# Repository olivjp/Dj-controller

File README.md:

# Pioneer DDJ-FLX4 Modular Core v2.3 — Open-Source 2-Deck USB-MIDI DJ Controller

Hardware (**KiCad 9.0** `98 × 98 mm` 2-Layer Core PCB — **0 ERC / 0 DRC / 0 unconnected**, ~US\$ 2 na JLCPCB), chassi 3D imprimível em PLA (**FreeCAD 1.0** `.step`/`.stl` em 3 módulos `≤ 115 × 206 mm` compatíveis com cama `220 × 220 mm`, **0 colisões P0** após 3 rodadas independentes de auditoria), e firmware USB-MIDI nativo (**ATmega32U4** com ISRs `PIND` atômicas, varredura Gray, Pitch 14-bit e script JS para **Mixxx 2.4+**).

---

## 1. Visual Previews

### KiCad 9.0 3D Raytraced Core PCB (`98 × 98 mm`, 2-Layer FR4, Solid `B.Cu` GND Plane)

### FreeCAD 1.0 3D-Printable Enclosure Assembly (`340 × 206 × 45.5 mm`)

---

## 2. Arquitetura Modular Core v2.3 (Consolidada após 3 Rodadas de Auditoria)

1. **Placa-Mãe Central `98 × 98 mm`, 2 Camadas (`100% THT 2.54 mm`):**
   - **Arduino Pro Micro USB-C (`J1`/`J2`):** `RAW` (`J2.1`) e `RST` (`J2.3`) desconectados (`NC`).
   - **2× Módulos Breakout Azuis `CD74HC4067` (`J3/J4` = `U1` Analógico com `C15` no topo; `J5/J6` = `U2` Pads girado `180°` com `C0` no topo):** casados 1:1 com o módulo azul físico (`1×16` `C15..C0` + `1×8` `SIG, S3, S2, S1, S0, EN, VCC, GND` alinhado a `C11..C4`, passo `15.24 mm`). *Fazer teste de continuidade A1 antes de subir o Gerber.*
   - **Front-End Analógico Baixo-Crosstalk:** `16×` capacitores `100 nF` (`C10..C25`) **ANTES** do multiplexador `U1` + `R1 = 100 Ω` com **`C3 = DNP`** (não montar `C3`, mantendo o resíduo de carga em `0.22–0.37 LSB` em vez de `3.6–6.2 LSB`).
   - **Debounce de Encoders Padrão Alps (`ENC1`/`ENC2`):** `10 kΩ` pull-up (`R3..R6`) + `10 kΩ` série anti-pitting (`R12..R15`) + `10 nF` (`C4..C7`), compatível com os limiares LVTTL reais do ATmega32U4 ($V_{IL} \le 0.90\text{ V}$, $V_{IH} \ge 1.90\text{ V}$).
   - **Plano de Terra Sólido (`B.Cu`):** `0` violações DRC, `0` itens desconectados (`hardware/gerbers/ddj_flx4_core_v2_jlcpcb.zip`).
2. **Chassi 3D Modular v2.3 (`340 × 206 × 45.5 mm`, `BOTTOM_H = 42 mm`) — 0 Colisões P0:**
   - **PCB recuada `0.5 mm` da parede traseira (`PCB_Y_REAR = 201.5 mm`):** furos traseiros `H1/H2` (`126.08, 196.42` / `213.71, 196.42`) usam **`M3×12` cabeça cilíndrica por baixo** + **espaçador de latão F-F `M3×30` (`5.5 AF`)** + boss `Ø 7 × 1.4 mm` sob a faceplate (`M3×10` escareado por cima). Tirar a tampa não solta a PCB e mantém `+0.71..+1.21 mm` de folga até `RV1/RV6`.
   - **Lábio (`WALL_T + 0.5 mm`) e nervuras de emenda com alívio `Ø 11 mm`** nos 10 pilares + `H1/H2`.
   - **Recorte USB-C alinhado em `Z = -25.2 .. -9.2 mm`** (acomoda overmold até `8.5 mm`).
   - **6 Carriers rígidos com orelhas (`ddj_flx4_switch_carriers.stl`):** `deckA_frente`, `deckB_frente`, `mixer_top`, `mixer_cue`, `loopsync_A`, `loopsync_B`, base `±8.2 mm` (parede sólida por fora dos rasgos de pinos `±7.15 mm`), todos os 30 switches dentro da envoltória convexa de apoio (`margem ≥ +1.0 mm`, alcance `≤ 14.9 mm`), empacotamento automático sem sobreposição, `CARRIER_STANDOFF_H = 4.5 mm` (ajustar para `5.6 mm` se o atuador `G82` medir `≥ Ø 7.2 mm`).
   - **Jog Wheels (`Ø 84 mm`) + Faceplate cheia (`3.5 mm`, sem rebaixo `Ø 86`):** trava de porca `M3` em `r = 6.8..9.2 mm` (livre do rebaixo sob o cubo `Ø 12.5 × 4.0 mm`), canal de acesso `Ø 3.4 mm` para **grub `M3×8`**.
   - **Emendas:** blocos até `Z = -3.0 mm` apoiando as nervuras da faceplate + **4× `M3×12` horizontais por emenda** (`Y = 28` em `Z = -8, -34`; `Y = 178` em `Z = -8, -20` — livres da PCB, de `J9/J10` e de `loopsync_B`).
3. **Firmware USB-MIDI v2.3 + Mixxx 2.4+ (`firmware/`):**
   - Varredura do mux em **código Gray cíclico** (`{0,1,3,2,6,7,5,4,12,13,15,14,10,11,9,8}` — sempre 1 bit por troca entre `PD4/PC6/PD7/PE6`).
   - **`#define HAS_RV16 0`:** pula *apenas* o bloco analógico de `U1` no canal `15` (mantém `SW16` / Pad 8 Deck B e a sequência Gray intactos; nunca usar jumper em `POT_CH15`).
   - **Matriz 4×4 em Open-Drain:** linhas inativas em `INPUT` (Hi-Z), eliminando risco de curto `> 40 mA` caso um diodo `1N4148` fique invertido.
   - **Histerese aplicada sobre o `filtered` cru antes da LUT**, linearização nos **5 faders `D103`** (`CH10..CH14`), zona morta central no Pitch 14-bit (`0xE0`/`0xE1`), `beatloop_toggle` e `SMART_CFX`/`BEAT_FX` nos 2 decks no Mixxx.

---

## 3. Checklist de Bancada (Antes de Fabricar / Imprimir)

| # | Medição física | Objetivo |
|---|---|---|
| **A1** | Módulo azul `CD74HC4067`: encaixe a seco (componentes p/ cima, `1×16` à esquerda, USB-C longe de você $\rightarrow$ canto superior = `C15` alinhado a `SIG`) + continuidade `GND↔pino 12`, `C0↔9`, `C15↔16` e passo `15.24 mm` | **P0** — Libera `ddj_flx4_core_v2_jlcpcb.zip` na JLCPCB |
| **A2** | Diâmetro do atuador do switch `G82` | `CARRIER_STANDOFF_H = 4.5 mm` (`< Ø 7.2`) ou `5.6 mm` (`≥ Ø 7.2`) |
| **A3** | Altura do `WH148` + fio soldado abaixo da faceplate + diâmetro real do corpo (`r ≤ 8.5 mm`) | Folga em Z = `0.8 mm` (se `> 16 mm`, dobrar terminais ou usar `BOTTOM_H = 44`) |
| **A4** | `EC11`: comprimento da bucha M7, comprimento do eixo (`15` vs `20 mm`) e trecho D-flat | Confirmar `JOG_Z` e cota `Z = 4.5 mm` do grub `M3×8` |
| **A5** | Medir fader `D103` no multímetro a `0 / 25 / 50 / 75 / 100%` | Ajustar `LOG_INV_LUT` (ou desligar `LINEARIZE_D103_LOG_FADERS` se linear) |

---

## 4. Bill of Materials (BOM v2.3)

### Na Placa-Mãe Central (`98 × 98 mm` — `hardware/gerbers/ddj_flx4_core_v2_jlcpcb.zip`)
| Designator | Qty | Componente | Observação |
| :--- | :---: | :--- | :--- |
| `J1`, `J2` | 1 | **Arduino Pro Micro USB-C (`ATmega32U4 5V 16MHz`)** + 2× barras fêmea `1×12` | Soquetado rente à borda traseira |
| `J3/J4`, `J5/J6` | 2 | **Módulo Breakout `CD74HC4067` (16-ch, 2.54mm THT)** + barras fêmea `1×16` & `1×8` | `U2` montado girado `180°` |
| `J7..J14` | 8 | Barras de pinos `2.54 mm` (`3× 1×8`, `2× 1×10`, `2× 1×6`, `1× 1×4`) | Chicotes p/ controles de painel |
| `C10..C25`, `C1,C2,C8` | 19 | Capacitores cerâmicos **`100 nF (104)`** THT (`P5.0mm`) | 16× filtro pré-mux + 3× desacoplamento |
| `C3` | 0 | **`DNP` (Não montar)** | Deixar vazio p/ evitar compartilhamento de carga |
| `C4..C7` | 4 | Capacitores cerâmicos **`10 nF (103)`** THT (`P5.0mm`) | Debounce EC11 |
| `R2..R10`, `R12..R15` | 13 | Resistores **`10 kΩ`** 1/4W axial (`P7.62mm`) | Pull-ups + 4× série anti-pitting EC11 |
| `R1`, `R11` | 2 | `1× 100 Ω` (`R1` ADC) + `1× 330 Ω` (`R11` LED) | 1/4W axial |
| `D17` | 1 | LED `5 mm` Verde (Power) | Opcional: puxar com 2 fios p/ furo da faceplate |

### No Painel 3D (Off-Board) e Ferragens M3 (v2.3)
| Designator | Qty | Componente |
| :--- | :---: | :--- |
| `RV1..RV10` (+ `RV16` opc.) | 10–11 | Potenciômetros rotativos **`WH148 B10K`** (`10 kΩ` linear) + knobs `6 mm` (`HAS_RV16 = 0` se usar 10) |
| `RV11..RV15` | 5 | Faders deslizantes **`D103 = D10K×2` (`75 mm` / `60 mm` curso)** + tampas + `10×` parafusos `M2.5` |
| `SW1..SW30` | 30 | Switches táteis **`G82 12×12×5 mm`** |
| `ENC1`, `ENC2` | 2 | Encoders rotativos **`EC11`** (preferir sem detent) com push-switch |
| `D1..D16` | 16 | Diodos **`1N4148`** (matriz 4×4 anti-ghosting) |
| **Ferragens M3 (v2.3)** | 1 kit | `10× M3×45` escareados (pilares) + `2× M3×12` cabeça cilíndrica + `2×` espaçador latão F-F `M3×30` (`5.5 AF`) + `2× M3×10` escareados (H1/H2) + `2× M3×10` (H3/H4 PCB) + `40× M3×6` (6 carriers) + `2×` grub `M3×8` + `2×` porcas `M3` (jogs) + `8× M3×12` + `8×` porcas + `16×` arruelas (emendas) + `12×` porcas `M3` (pilares/H3/H4) + `6×` pezinhos de silicone |

---

## 5. Ordem de Impressão 3D em PLA

1. **Primeiro (~8 g, 15 min):** `cad/stl/ddj_flx4_tolerance_test.stl` (validar folgas da impressora).
2. **Base (`42 mm`, 3 módulos `≤ 115 × 206 mm`):** `ddj_flx4_bottom_left_deckA.stl`, `ddj_flx4_bottom_center_mixer.stl`, `ddj_flx4_bottom_right_deckB.stl`.
3. **Faceplate (3 módulos, imprimir de cabeça para baixo):** `ddj_flx4_top_left_deckA.stl`, `ddj_flx4_top_center_mixer.stl`, `ddj_flx4_top_right_deckB.stl`.
4. **Carriers dos 30 Switches `G82` (6 placas com orelhas em 1 mesa):** `cad/stl/ddj_flx4_switch_carriers.stl`.
5. **Controles:** `2× ddj_flx4_jog_wheel.stl` + `30× ddj_flx4_pad_keycap.stl`.

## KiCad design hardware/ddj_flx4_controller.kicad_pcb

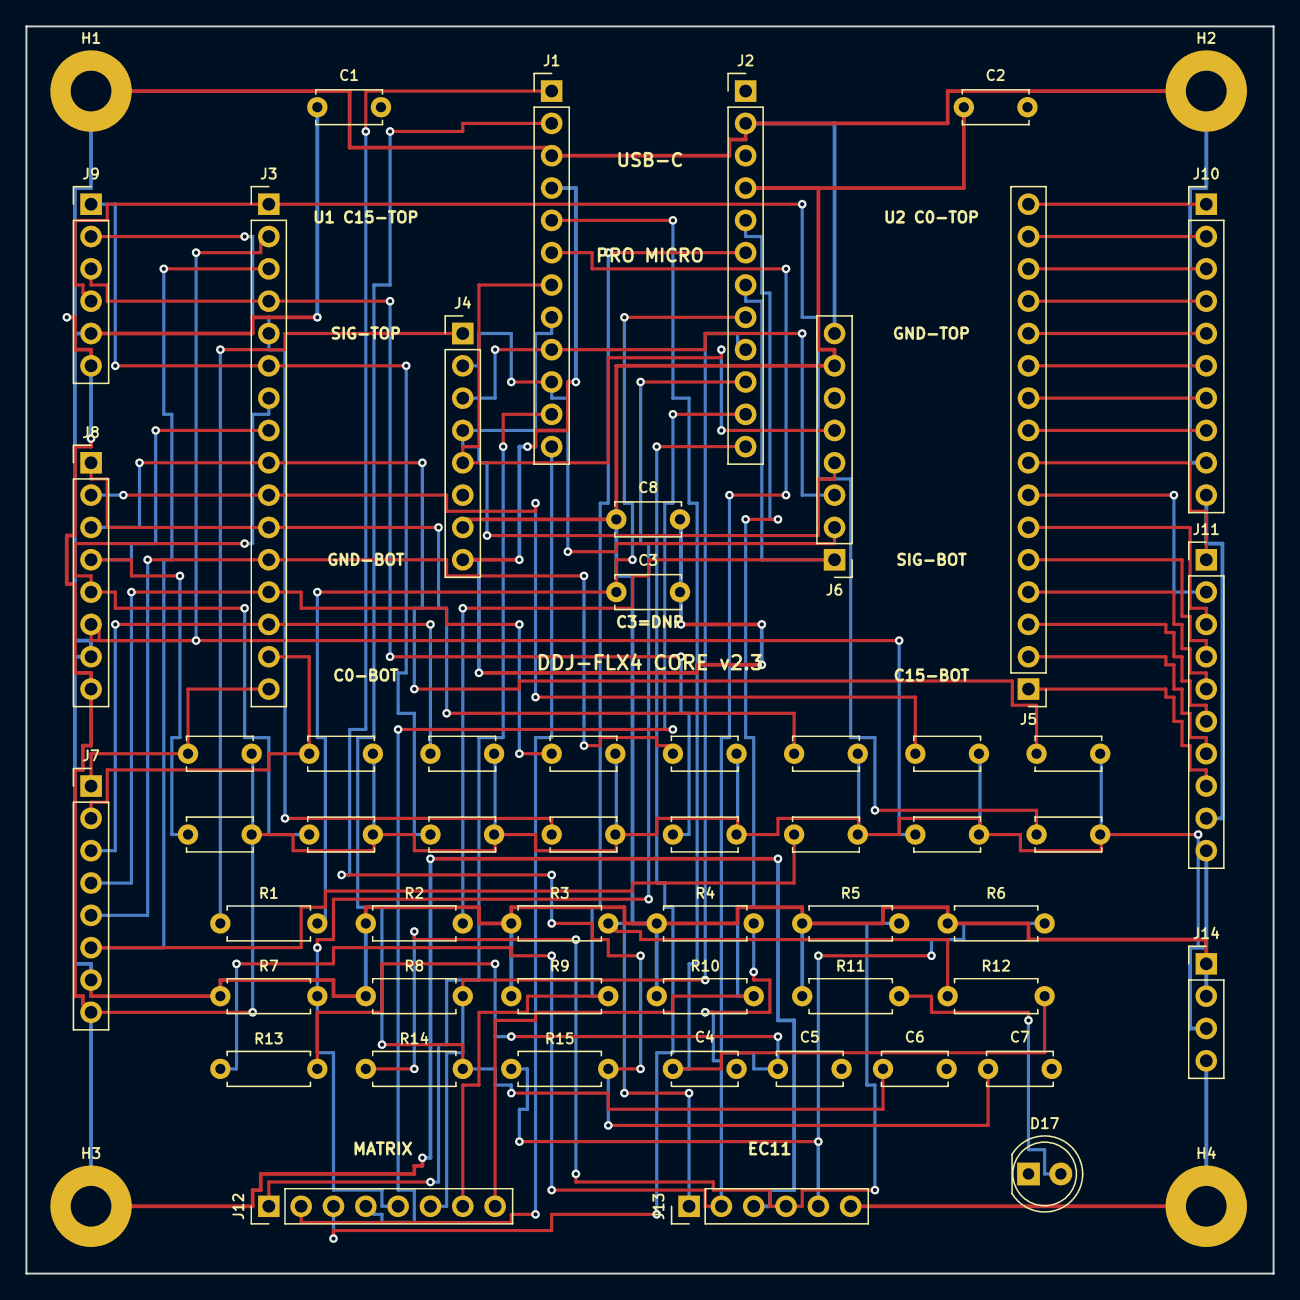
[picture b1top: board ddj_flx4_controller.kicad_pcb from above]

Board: 2 copper layers, 98.0 x 98.0 mm, 58 parts (0 on the bottom side), 58 nets.

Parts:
C1: 100nF_U1_DEC; C_Disc_D5.0mm_W2.5mm_P5.00mm
C2: 100nF_U2_DEC; C_Disc_D5.0mm_W2.5mm_P5.00mm
C3: DNP_OPT_100pF; C_Disc_D5.0mm_W2.5mm_P5.00mm
C4: 10nF_ENC1A; C_Disc_D5.0mm_W2.5mm_P5.00mm
C5: 10nF_ENC1B; C_Disc_D5.0mm_W2.5mm_P5.00mm
C6: 10nF_ENC2A; C_Disc_D5.0mm_W2.5mm_P5.00mm
C7: 10nF_ENC2B; C_Disc_D5.0mm_W2.5mm_P5.00mm
C8: 100nF_MCU_DEC; C_Disc_D5.0mm_W2.5mm_P5.00mm
C10: 100nF_POT0; C_Disc_D5.0mm_W2.5mm_P5.00mm
C11: 100nF_POT1; C_Disc_D5.0mm_W2.5mm_P5.00mm
C12: 100nF_POT2; C_Disc_D5.0mm_W2.5mm_P5.00mm
C13: 100nF_POT3; C_Disc_D5.0mm_W2.5mm_P5.00mm
C14: 100nF_POT4; C_Disc_D5.0mm_W2.5mm_P5.00mm
C15: 100nF_POT5; C_Disc_D5.0mm_W2.5mm_P5.00mm
C16: 100nF_POT6; C_Disc_D5.0mm_W2.5mm_P5.00mm
C17: 100nF_POT7; C_Disc_D5.0mm_W2.5mm_P5.00mm
C18: 100nF_POT8; C_Disc_D5.0mm_W2.5mm_P5.00mm
C19: 100nF_POT9; C_Disc_D5.0mm_W2.5mm_P5.00mm
C20: 100nF_POT10; C_Disc_D5.0mm_W2.5mm_P5.00mm
C21: 100nF_POT11; C_Disc_D5.0mm_W2.5mm_P5.00mm
C22: 100nF_POT12; C_Disc_D5.0mm_W2.5mm_P5.00mm
C23: 100nF_POT13; C_Disc_D5.0mm_W2.5mm_P5.00mm
C24: 100nF_POT14; C_Disc_D5.0mm_W2.5mm_P5.00mm
C25: 100nF_POT15; C_Disc_D5.0mm_W2.5mm_P5.00mm
D17: LED_PWR_GREEN; LED_D5.0mm
H1, H2, H3, H4: M3_Mount_GND; MountingHole_3.2mm_M3_Pad
J1: ProMicro_Left_1x12; PinHeader_1x12_P2.54mm_Vertical
J2: ProMicro_Right_1x12; PinHeader_1x12_P2.54mm_Vertical
J3: U1_CD74HC4067_CH_1x16; PinHeader_1x16_P2.54mm_Vertical
J4: U1_CD74HC4067_CTRL_1x8; PinHeader_1x08_P2.54mm_Vertical
J5: U2_CD74HC4067_CH_1x16; PinHeader_1x16_P2.54mm_Vertical
J6: U2_CD74HC4067_CTRL_1x8; PinHeader_1x08_P2.54mm_Vertical
J7: HDR_POTS_DECK_A; PinHeader_1x08_P2.54mm_Vertical
J8: HDR_POTS_DECK_B; PinHeader_1x08_P2.54mm_Vertical
J9: HDR_MIXER_FADERS; PinHeader_1x06_P2.54mm_Vertical
J10: HDR_PADS_DECK_A; PinHeader_1x10_P2.54mm_Vertical
J11: HDR_PADS_DECK_B; PinHeader_1x10_P2.54mm_Vertical
J12: HDR_MATRIX_4x4; PinHeader_1x08_P2.54mm_Vertical
J13: HDR_ENCODERS_EC11; PinHeader_1x06_P2.54mm_Vertical
J14: HDR_PWR_AUX; PinHeader_1x04_P2.54mm_Vertical
R1: 100R_ADC_SER; R_Axial_DIN0207_L6.3mm_D2.5mm_P7.62mm_Horizontal
R2: 10k_PADS_PU; R_Axial_DIN0207_L6.3mm_D2.5mm_P7.62mm_Horizontal
R3: 10k_ENC1A_PU; R_Axial_DIN0207_L6.3mm_D2.5mm_P7.62mm_Horizontal
R4: 10k_ENC1B_PU; R_Axial_DIN0207_L6.3mm_D2.5mm_P7.62mm_Horizontal
R5: 10k_ENC2A_PU; R_Axial_DIN0207_L6.3mm_D2.5mm_P7.62mm_Horizontal
R6: 10k_ENC2B_PU; R_Axial_DIN0207_L6.3mm_D2.5mm_P7.62mm_Horizontal
R7: 10k_COL0_PU; R_Axial_DIN0207_L6.3mm_D2.5mm_P7.62mm_Horizontal
R8: 10k_COL1_PU; R_Axial_DIN0207_L6.3mm_D2.5mm_P7.62mm_Horizontal
R9: 10k_COL2_PU; R_Axial_DIN0207_L6.3mm_D2.5mm_P7.62mm_Horizontal
R10: 10k_COL3_PU; R_Axial_DIN0207_L6.3mm_D2.5mm_P7.62mm_Horizontal
R11: 330R_LED_PWR; R_Axial_DIN0207_L6.3mm_D2.5mm_P7.62mm_Horizontal
R12: 10k_ENC1A_SER; R_Axial_DIN0207_L6.3mm_D2.5mm_P7.62mm_Horizontal
R13: 10k_ENC1B_SER; R_Axial_DIN0207_L6.3mm_D2.5mm_P7.62mm_Horizontal
R14: 10k_ENC2A_SER; R_Axial_DIN0207_L6.3mm_D2.5mm_P7.62mm_Horizontal
R15: 10k_ENC2B_SER; R_Axial_DIN0207_L6.3mm_D2.5mm_P7.62mm_Horizontal

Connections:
+5V: C1.1, C2.1, C8.1, J2.4, J4.7, J6.7, J7.7, J8.7, J9.5, J14.1, J14.2, R2.1, R3.1, R4.1, R5.1, R6.1, R7.1, R8.1, R9.1, R10.1, R11.1
COL0: J2.10, J12.5, R7.2
COL1: J2.9, J12.6, R8.2
COL2: J2.6, J12.7, R9.2
COL3: J2.5, J12.8, R10.2
ENC1_A: C4.1, J1.5, R12.2
ENC1_A_RAW: J13.1, R3.2, R12.1
ENC1_B: C5.1, J1.6, R13.2
ENC1_B_RAW: J13.2, R4.2, R13.1
ENC2_A: C6.1, J1.2, R14.2
ENC2_A_RAW: J13.4, R5.2, R14.1
ENC2_B: C7.1, J1.1, R15.2
ENC2_B_RAW: J13.5, R6.2, R15.1
GND: C1.2, C2.2, C3.2, C4.2, C5.2, C6.2, C7.2, C8.2, C10.2, C11.2, C12.2, C13.2, C14.2, C15.2, C16.2, C17.2, C18.2, C19.2, C20.2, C21.2, C22.2, C23.2, C24.2, C25.2, D17.1, H1.1, H2.1, H3.1, H4.1, J1.3, J1.4, J2.2, J4.6, J4.8, J6.6, J6.8, J7.8, J8.8, J9.6, J10.9, J10.10, J11.9, J11.10, J13.3, J13.6, J14.3, J14.4
LED_PWR_A: D17.2, R11.2
MUX1_ADC: C3.1, J2.8, R1.2
MUX1_COM: J4.1, R1.1
MUX2_COM: J2.7, J6.1, R2.2
MUX_S0: J1.7, J4.5, J6.5
MUX_S1: J1.8, J4.4, J6.4
MUX_S2: J1.9, J4.3, J6.3
MUX_S3: J1.10, J4.2, J6.2
PAD_CH0: J5.16, J10.1
PAD_CH1: J5.15, J10.2
PAD_CH2: J5.14, J10.3
PAD_CH3: J5.13, J10.4
PAD_CH4: J5.12, J10.5
PAD_CH5: J5.11, J10.6
PAD_CH6: J5.10, J10.7
PAD_CH7: J5.9, J10.8
PAD_CH8: J5.8, J11.1
PAD_CH9: J5.7, J11.2
PAD_CH10: J5.6, J11.3
PAD_CH11: J5.5, J11.4
PAD_CH12: J5.4, J11.5
PAD_CH13: J5.3, J11.6
PAD_CH14: J5.2, J11.7
PAD_CH15: J5.1, J11.8
POT_CH0: C10.1, J3.16, J7.1
POT_CH1: C11.1, J3.15, J7.2
POT_CH2: C12.1, J3.14, J7.3
POT_CH3: C13.1, J3.13, J7.4
POT_CH4: C14.1, J3.12, J7.5
POT_CH5: C15.1, J3.11, J8.1
POT_CH6: C16.1, J3.10, J8.2
POT_CH7: C17.1, J3.9, J8.3
POT_CH8: C18.1, J3.8, J8.4
POT_CH9: C19.1, J3.7, J8.5
POT_CH10: C20.1, J3.6, J9.1
POT_CH11: C21.1, J3.5, J9.2
POT_CH12: C22.1, J3.4, J9.3
POT_CH13: C23.1, J3.3, J7.6
POT_CH14: C24.1, J3.2, J8.6
POT_CH15: C25.1, J3.1, J9.4
ROW0: J1.11, J12.1
ROW1: J1.12, J12.2
ROW2: J2.12, J12.3
ROW3: J2.11, J12.4

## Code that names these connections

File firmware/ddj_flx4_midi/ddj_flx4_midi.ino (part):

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}

// ── Pin Definitions (Matched 1:1 with v2 98x98mm Core PCB) ───────────────────
constexpr uint8_t PIN_ENC2_A = 0;  // PD2 / INT2
constexpr uint8_t PIN_ENC2_B = 1;  // PD3 / INT3
constexpr uint8_t PIN_ENC1_A = 2;  // PD1 / INT1
constexpr uint8_t PIN_ENC1_B = 3;  // PD0 / INT0

constexpr uint8_t PIN_MUX_S0 = 4;
constexpr uint8_t PIN_MUX_S1 = 5;
constexpr uint8_t PIN_MUX_S2 = 6;
constexpr uint8_t PIN_MUX_S3 = 7;

constexpr uint8_t PIN_MUX1_ANALOG = A0;  // U1 SIG (16 Pots/Faders, pre-mux 100nF filtered)
constexpr uint8_t PIN_MUX2_PADS   = A1;  // U2 SIG (16 Performance Pads, external 10k pull-up)
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};

// ── Atomic Hardware Interrupt Service Routines (PIND = 1 CPU cycle = 62.5ns) ─
// ATmega32U4: PD1=D2(ENC1_A), PD0=D3(ENC1_B), PD2=D0(ENC2_A), PD3=D1(ENC2_B)
void isrEnc1() {
  uint8_t cur = PIND & 0x03; // (PD1 << 1) | PD0 = (ENC1_A << 1) | ENC1_B
  jogDeltaA += ENC_TABLE[(prevEncA << 2) | cur];
  prevEncA = cur;
}
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}

inline void selectMuxChannel(uint8_t ch) {
  digitalWrite(PIN_MUX_S0, (ch & 0x01) ? HIGH : LOW);
  digitalWrite(PIN_MUX_S1, (ch & 0x02) ? HIGH : LOW);
  digitalWrite(PIN_MUX_S2, (ch & 0x04) ? HIGH : LOW);
  digitalWrite(PIN_MUX_S3, (ch & 0x08) ? HIGH : LOW);
  delayMicroseconds(25); // Settles C3<=1nF + mux R_on + pre-mux 100nF bank completely
}

void setup() {
  pinMode(PIN_MUX_S0, OUTPUT);
  pinMode(PIN_MUX_S1, OUTPUT);
  pinMode(PIN_MUX_S2, OUTPUT);
  pinMode(PIN_MUX_S3, OUTPUT);

  pinMode(PIN_MUX1_ANALOG, INPUT);
  pinMode(PIN_MUX2_PADS, INPUT); // External R2=10k pull-up on Core PCB

  // External 10k pull-up + 10k series + 10nF Alps RC on Core PCB (no parallel internal pull-up)
  pinMode(PIN_ENC1_A, INPUT);
  pinMode(PIN_ENC1_B, INPUT);
  pinMode(PIN_ENC2_A, INPUT);
  pinMode(PIN_ENC2_B, INPUT);

  prevEncA = PIND & 0x03;
  uint8_t p = PIND;
  prevEncB = ((p & _BV(PD2)) ? 2 : 0) | ((p & _BV(PD3)) ? 1 : 0);

  attachInterrupt(digitalPinToInterrupt(PIN_ENC1_A), isrEnc1, CHANGE);
  attachInterrupt(digitalPinToInterrupt(PIN_ENC1_B), isrEnc1, CHANGE);
  attachInterrupt(digitalPinToInterrupt(PIN_ENC2_A), isrEnc2, CHANGE);
  attachInterrupt(digitalPinToInterrupt(PIN_ENC2_B), isrEnc2, CHANGE);

  // 4x4 Diode-Isolated Switch Matrix (open-drain: inactive rows kept INPUT Hi-Z to prevent >40mA shorts!)
  for (uint8_t r = 0; r < 4; r++) {
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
